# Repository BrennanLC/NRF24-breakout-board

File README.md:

# NRF24-breakout-board
nRF24 breakout board for development

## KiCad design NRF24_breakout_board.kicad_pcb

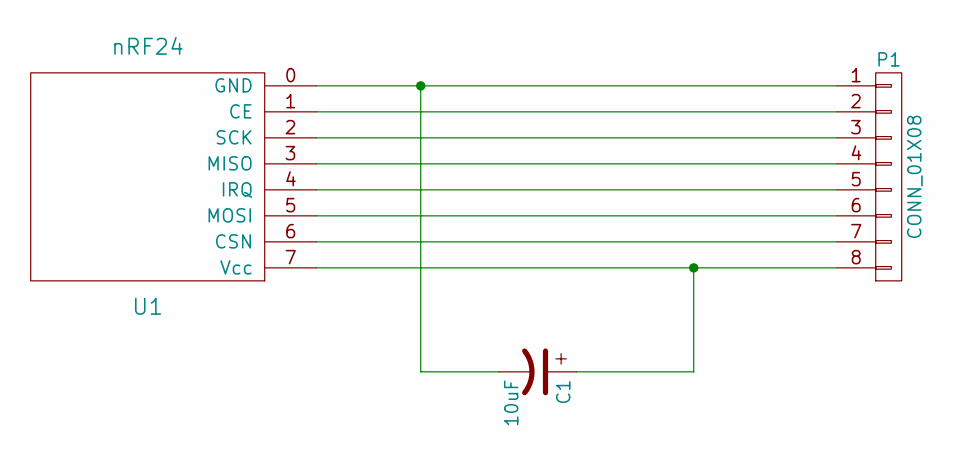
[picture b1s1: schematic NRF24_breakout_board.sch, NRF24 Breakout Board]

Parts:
C1: 10uF; C_Radial_D10_L16_P5
P1: CONN_01X08; Pin_Header_Straight_1x08
U1: nRF24

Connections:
unnamed: C1.1, P1.8, U1.7 (Vcc)
unnamed: C1.2, P1.1, U1.0 (GND)
unnamed: P1.2, U1.1 (CE)
unnamed: P1.3, U1.2 (SCK)
unnamed: P1.4, U1.3 (MISO)
unnamed: P1.5, U1.4 (IRQ)
unnamed: P1.6, U1.5 (MOSI)
unnamed: P1.7, U1.6 (CSN)

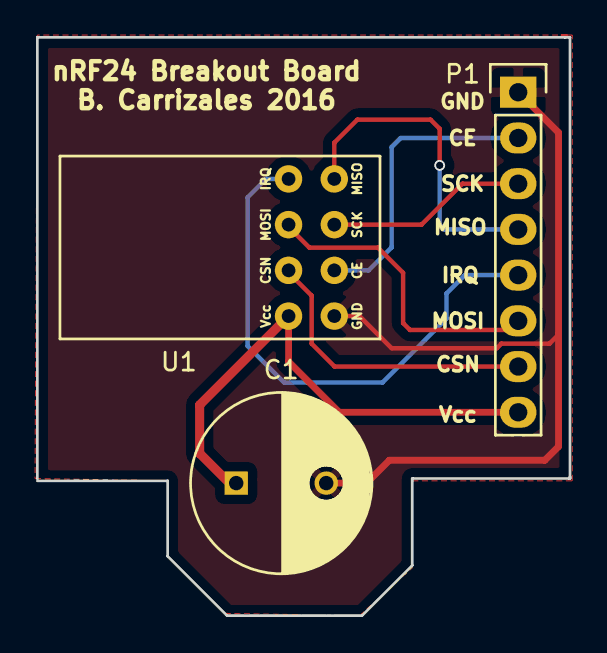
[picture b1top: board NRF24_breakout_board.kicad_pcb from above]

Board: 2 copper layers, 29.6 x 32.1 mm, 3 parts (0 on the bottom side), 8 nets.

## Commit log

2016-09-05 Create README file
2016-09-05 commit README
    add README file
